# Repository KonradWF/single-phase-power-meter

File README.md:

# Single-Phase power meter!

The device is used to measure electric power from a single-phase electrical grid.
The following electrical network parameters can be measured with the device:
* Voltage V
* Current I
* Power P
* Reactive Power Q
* Apparent Power S
* Power Factor PF

## Authors 
- Konrad Fiałkowski
- Michał Krzyworzeka
- Bartłomiej Paluch

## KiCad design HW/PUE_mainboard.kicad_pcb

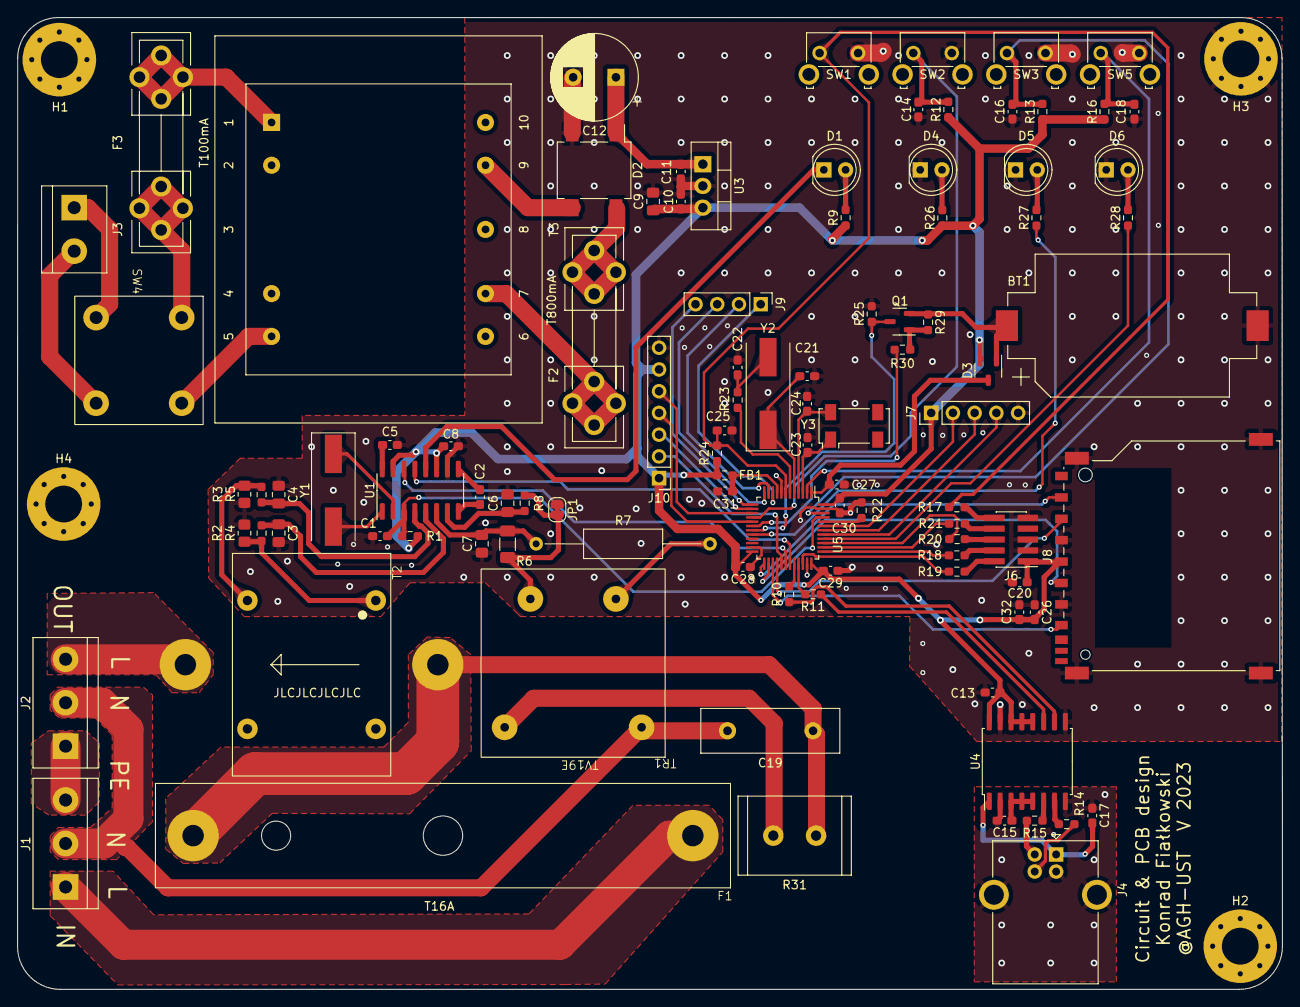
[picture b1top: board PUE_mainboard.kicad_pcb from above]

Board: 2 copper layers, 147.8 x 113.6 mm, 104 parts (0 on the bottom side), 91 nets.

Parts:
BT1: Battery_Cell; BatteryHolder_Keystone_1060_1x2032
C1, C2, C5, C8, C10, C11, C13, C14, C15, C16, C17, C18, C20, C25, C26, C27, C28, C29, C30, C31: 100n; C_0603_1608Metric_Pad1.08x0.95mm_HandSolder
C3, C4, C6, C7: 27n; C_0805_2012Metric_Pad1.18x1.45mm_HandSolder
C9: 10u; C_0805_2012Metric_Pad1.18x1.45mm_HandSolder
C12: 1000u/25V; CP_Radial_D10.0mm_P5.00mm
C19: C; C_Disc_D16.0mm_W5.0mm_P10.00mm
C21, C22: 18p; C_0603_1608Metric_Pad1.08x0.95mm_HandSolder
C23, C24: 12,5p; C_0603_1608Metric_Pad1.08x0.95mm_HandSolder
C32: 1u; C_0603_1608Metric_Pad1.08x0.95mm_HandSolder
D1, D4, D5, D6: LED; LED_D5.0mm
D2: D_Bridge_+-AA; Diode_Bridge_Vishay_DFS
D3: D_Schottky_Dual_CommonCathode_AAK; SOT-23-3
F1: Fuse 20A; BK2-S-4201-1-R
F2: T500mA; Fuseholder5x20_horiz_open_universal_Type-III
F3: T100mA; Fuseholder5x20_horiz_open_universal_Type-III
FB1: FerriteBead; R_0603_1608Metric_Pad0.98x0.95mm_HandSolder
H1, H2, H3, H4: MountingHole; MountingHole_4.3mm_M4_Pad_Via
J1, J2: Conn_01x03_Male; TerminalBlock_bornier-3_P5.08mm
J3: Conn_01x02_Male; TerminalBlock_bornier-2_P5.08mm
J4: USB_B; USB_B_OST_USB-B1HSxx_Horizontal
J6: Conn_ARM_JTAG_SWD_10; PinHeader_2x05_P1.27mm_Vertical_SMD
J7: Conn_01x05_Pin; PinHeader_1x05_P2.54mm_Vertical
J8: SD_Card; SD_TE_2041021
J9: Conn_01x04_Pin; PinHeader_1x04_P2.54mm_Vertical
J10: Conn_01x07_Pin; PinHeader_1x07_P2.54mm_Vertical
JP1: Jumper_2_Bridged; SolderJumper-2_P1.3mm_Bridged_RoundedPad1.0x1.5mm
Q1: Q_PMOS_GSD; SOT-23-3
R1, R12, R13, R16, R22, R24, R25, R29: 10k; R_0603_1608Metric_Pad0.98x0.95mm_HandSolder
R2, R3: 25R; R_0805_2012Metric_Pad1.20x1.40mm_HandSolder
R4, R5, R8: 1k; R_0603_1608Metric_Pad0.98x0.95mm_HandSolder
R6: 50R; R_1206_3216Metric_Pad1.30x1.75mm_HandSolder
R7: 450R, 0,25W; R_Axial_DIN0309_L9.0mm_D3.2mm_P20.32mm_Horizontal
R9: 470R; R_0603_1608Metric_Pad0.98x0.95mm_HandSolder
R10, R11, R14, R15: 24R; R_0603_1608Metric_Pad0.98x0.95mm_HandSolder
R17, R18, R19, R20, R21, R30: 100R; R_0603_1608Metric_Pad0.98x0.95mm_HandSolder
R23: 390R; R_0603_1608Metric_Pad0.98x0.95mm_HandSolder
R26, R27, R28: 33R; R_0603_1608Metric_Pad0.98x0.95mm_HandSolder
R31: 100k; 300V; R_Radial_Power_L13.0mm_W9.0mm_P5.00mm
SW1, SW2, SW3, SW5: SW_Push; SW_SPST_Omron_B3F-315x_Angled
SW4: SW_DPST; mains_switch
T2: TA14Z-400
T3: TEZ 6,0/D 230/7,5V; Transformer_Breve_TEZ-38x45
TR1: TV19E
U1: CS5490; SOIC-16_3.9x9.9mm_P1.27mm
U3: LMS8117A; TO-220-3_Vertical
U4: ADUM3160; SOIC-16W_7.5x10.3mm_P1.27mm
U5: STM32F103C8Tx; LQFP-48_7x7mm_P0.5mm
Y1: Crystal_4,096MHz; Crystal_SMD_HC49-SD
Y2: Crystal_16M; Crystal_SMD_HC49-SD
Y3: Crystal_32kHz; Crystal_SMD_Abracon_ABS25-4Pin_8.0x3.8mm

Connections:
+3V3: C8.2, C9.1, C10.1, C13.2, C20.1, C26.2, C28.2, C29.2, C30.2, C32.2, D3.2 (A), FB1.1, J6.1 (VTref), J7.1, J8.4 (VDD), J10.1, J10.6, R1.2, R9.1, R12.1, R13.1, R16.1, R24.2, R26.1, U1.11 (VDDA), U1.15 (MODE), U3.3 (VO), U4.12 (PIN), U4.13 (SPD), U4.14 (VDD2), U4.16 (VBUS2), U5.24 (VDD), U5.36 (VDD), U5.48 (VDD)
DC: J10.2, U5.29 (PA8)
FAIL_LED: R28.1, U5.40 (PB4)
GND: BT1.2 (-), C1.1, C3.2, C4.1, C5.1, C6.2, C7.1, C8.1, C9.2, C10.2, C11.2, C12.2, C13.1, C14.2, C16.2, C18.2, C20.2, C21.2, C22.2, C23.2, C24.2, C25.2, C26.1, C27.1, C28.1, C29.1, C30.1, C31.1, C32.1, D2.2 (-), D4.1 (K), D5.1 (K), D6.1 (K), H3.1, J6.3 (GND), J6.5 (GND), J6.9 (GNDDetect), J7.5, J8.3 (VSS), J8.6 (VSS), J8.12 (SHELL1), J10.7, JP1.1 (A), R2.2, R3.1, R22.2, R25.1, SW1.2, SW2.2, SW3.2, SW5.2, U1.10 (GNDA), U3.2 (GND), U4.9 (GND2), U4.15 (GND2), U5.8 (VSSA), U5.23 (VSS), U5.35 (VSS), U5.47 (VSS)
GND1: C15.1, C17.1, J4.4 (GND), J4.5 (Shield), U4.2 (GND1), U4.8 (GND1)
I2C_SCL: J7.3, U5.42 (PB6)
I2C_SDA: J7.2, U5.43 (PB7)
I2C_SMBAI: J7.4, U5.41 (PB5)
IIN+: C3.1, R4.1, U1.5 (IIN+)
IIN-: C4.2, R5.1, U1.4 (IIN-)
JTCK_SWCLK: R18.1, U5.37 (PA14)
JTDI: R21.1, U5.38 (PA15)
JTDO: R20.1, U5.39 (PB3)
JTMS_SWDIO: R19.1, U5.34 (PA13)
LOW_BATT_LED: R27.1, U5.20 (PB2)
unnamed: BT1.1 (+), D3.1 (A), Q1.2 (S), R29.1
unnamed: C19.1, F1.2, R31.1, T2.6
unnamed: C22.1, R23.2, Y2.2
unnamed: D1.2 (A), R9.2
unnamed: D1.1 (K), U1.12 (DO)
unnamed: C11.1, C12.1, D2.1 (+), U3.1 (VI)
unnamed: D2.3, T3.9
unnamed: D2.4, F2.2
unnamed: C27.2, D3.3 (K), U5.1 (VBAT)
unnamed: D4.2 (A), R26.2
unnamed: D5.2 (A), R27.2
unnamed: D6.2 (A), R28.2
unnamed: F2.1, T3.7
unnamed: F3.1, SW4.1
unnamed: F3.2, T3.1
unnamed: F1.1, J1.1
unnamed: C19.2, J1.2, J2.2, TR1.5
unnamed: J1.3, J2.1
unnamed: J2.3, T2.5
unnamed: J3.1, SW4.2
unnamed: J3.2, SW4.4
unnamed: J4.3 (D+), R14.1
unnamed: J4.2 (D-), R15.1
unnamed: C17.2, J4.1 (VBUS), U4.1 (VBUS1)
unnamed: J6.8 (NC/TDI), R21.2
unnamed: J6.4 (SWDCLK/TCK), R18.2
unnamed: J6.2 (SWDIO/TMS), R19.2
unnamed: J6.6 (SWO/TDO), R20.2
unnamed: J6.10 (~RESET), R17.2
unnamed: JP1.2 (B), R6.1, R8.2, TR1.9
unnamed: Q1.1 (G), R29.2, R30.2
unnamed: R2.1, R4.2, T2.1
unnamed: R3.2, R5.2, T2.2
unnamed: R7.2, TR1.7
unnamed: R31.2, TR1.1
unnamed: SW4.3, T3.5
unnamed: C5.2, U1.16 (VDDD)
unnamed: C2.1, U1.9 (VREF+)
unnamed: C2.2, U1.8 (VREF-)
unnamed: U1.2 (XIN), Y1.1
unnamed: U1.1 (XOUT), Y1.2
unnamed: R10.1, U4.10 (DD+)
unnamed: R11.1, U4.11 (DD-)
unnamed: C15.2, U4.3 (VDD1), U4.4 (PDEN), U4.5 (SPU)
unnamed: R14.2, U4.7 (UD+)
unnamed: R15.2, U4.6 (UD-)
unnamed: R22.1, U5.44 (BOOT0)
unnamed: C23.1, U5.3 (PC14), Y3.1
unnamed: C24.1, U5.4 (PC15), Y3.4
unnamed: C21.1, U5.5 (PD0), Y2.1
unnamed: R23.1, U5.6 (PD1)
unnamed: C31.2, FB1.2, U5.9 (VDDA)
RES: J10.3, U5.14 (PA4)
RESET: C25.1, R17.1, R24.1, SW1.1, U5.7 (NRST)
RESET_METER: C1.2, R1.1, U1.3 (RESET), U5.45 (PB8)
RX_TX: U1.14 (RX), U5.30 (PA9)
SPI1_MOSI: J10.4, U5.17 (PA7)
SPI1_SCK: J10.5, U5.15 (PA5)
SPI2_CS: J8.1 (CD/DAT3), U5.25 (PB12)
SPI2_MISO: J8.7 (DAT0), U5.27 (PB14)
SPI2_MOSI: J8.2 (CMD), U5.28 (PB15)
SPI2_SCK: J8.5 (CLK), U5.26 (PB13)
SW1: C14.1, R12.2, SW2.1, U5.16 (PA6)
SW2: C16.1, R13.2, SW3.1, U5.46 (PB9)
SW3: C18.1, R16.2, SW5.1, U5.2 (PC13)
TX_RX: U1.13 (TX), U5.31 (PA10)
USB_DD: R11.2, U5.33 (PA12)
USB_DM: R10.2, U5.32 (PA11)
VBAT_MEAS_ADC: Q1.3 (D), R25.2, U5.19 (PB1)
VBAT_MEAS_EN: R30.1, U5.18 (PB0)
VIN+: C7.2, R6.2, R7.1, U1.6 (VIN+)
VIN-: C6.1, R8.1, U1.7 (VIN-)
XL: J9.1, U5.10 (PA0)
XR: J9.3, U5.12 (PA2)
YD: J9.4, U5.13 (PA3)
YU: J9.2, U5.11 (PA1)

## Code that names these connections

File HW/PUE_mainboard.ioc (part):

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Mcu.Name=STM32F103C(8-B)Tx
Mcu.Package=LQFP48
Mcu.UserName=STM32F103C8Tx
PA0-WKUP.Signal=GPIO_Input
PA1.Signal=GPIO_Input
PA10.Mode=Asynchronous
PA10.Signal=USART1_RX
PA11.Mode=Device
PA11.Signal=USB_DM
PA12.Mode=Device
PA12.Signal=USB_DP
PA13.Mode=JTAG_4_pins
PA13.Signal=SYS_JTMS-SWDIO
PA14.Mode=JTAG_4_pins
PA14.Signal=SYS_JTCK-SWCLK
PA15.Mode=JTAG_4_pins
PA15.Signal=SYS_JTDI
PA2.Signal=GPIO_Input
PA3.Signal=GPIO_Input
PA4.Signal=GPIO_Input
PA5.Mode=TX_Only_Simplex_Unidirect_Master
PA5.Signal=SPI1_SCK
PA6.Signal=GPIO_Input
PA7.Mode=TX_Only_Simplex_Unidirect_Master
PA7.Signal=SPI1_MOSI
PA8.Signal=GPIO_Output
PA9.Mode=Asynchronous
PA9.Signal=USART1_TX
PB0.Signal=GPIO_Output
PB1.Signal=ADCx_IN9
PB12.Signal=SPI2_NSS
PB13.Mode=Full_Duplex_Master
PB13.Signal=SPI2_SCK
PB14.Mode=Full_Duplex_Master
PB14.Signal=SPI2_MISO
PB15.Mode=Full_Duplex_Master
PB15.Signal=SPI2_MOSI
PB2.Signal=GPIO_Output
PB3.Mode=JTAG_4_pins
PB3.Signal=SYS_JTDO-TRACESWO
PB4.Signal=GPIO_Output
PB5.Mode=SMBus-Alert-mode
PB5.Signal=I2C1_SMBA
PB6.Mode=SMBus-Alert-mode
PB6.Signal=I2C1_SCL
PB7.Mode=SMBus-Alert-mode
PB7.Signal=I2C1_SDA
PB8.Signal=GPIO_Output
PB9.Signal=GPIO_Input
PC13-TAMPER-RTC.Signal=GPIO_Input
PC14-OSC32_IN.Signal=RCC_OSC32_IN
PC15-OSC32_OUT.Signal=RCC_OSC32_OUT
PD0-OSC_IN.Signal=RCC_OSC_IN
PD1-OSC_OUT.Signal=RCC_OSC_OUT
board=custom

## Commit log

2023-05-07 Add final KiCad project files
2023-06-23 Add final version of the firmware
2023-06-24 Add PC Application
2023-06-24 Add Hardware Documentation
2023-06-26 Add Firmware documentation
2023-06-27 Add Instruction for PC Application
2023-06-28 Add README
